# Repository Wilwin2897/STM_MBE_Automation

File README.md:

"# STM_MBE_Automation" 
This is an application program that will provide users with a 
semi-automated platform for controlling the temperature of the substrate heating 
and effusion cells based on several important factors such as the pressure of the 
MBE chamber, together with an automated mechanism for opening and closing 
the cell's shutters. In this way, human errors could be minimized and the user is 
able to obtain all parameters in real-time which are essential for quality control.

Modular control is finished EXCEPT for: Beam Flux Monitor and Filament current source

Live plotting and data logging is only for STM+MBE Combivac pressure gauge, Eurotherms, Lakeshore336, TLC500, Load-Lock pressure Gauge, FUG Voltage

Effusion Cells power sources need to buy serial ethernet cable (which we don't have)
Filament current source and Beam flux monitor has not been integrated in the system

For tutorial on adding a new module, please check the main.py file, all details are included there. 

Hardware connection, just connect the ethernet cable from the network switch to your computer + USB serial cables for the FUG Pressure monitor

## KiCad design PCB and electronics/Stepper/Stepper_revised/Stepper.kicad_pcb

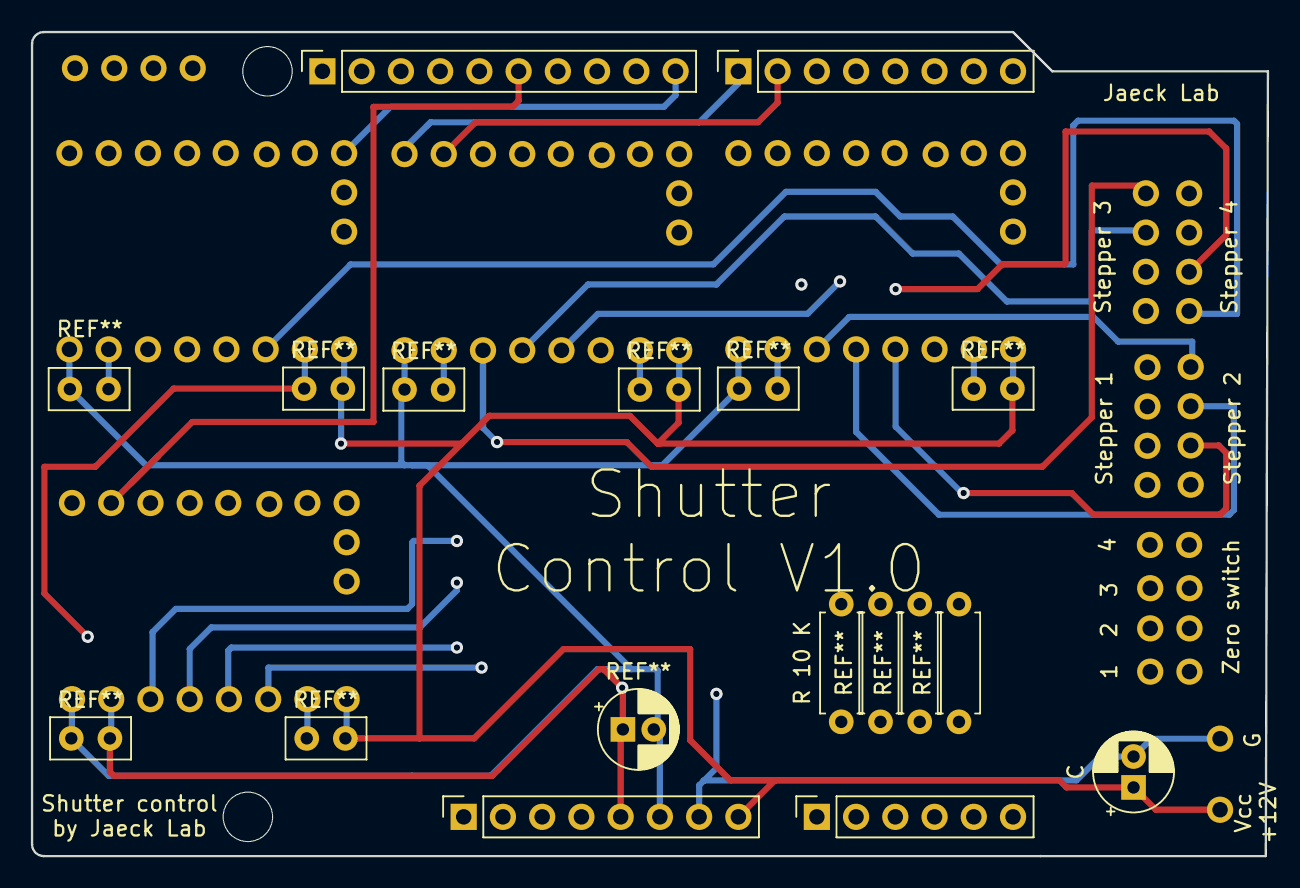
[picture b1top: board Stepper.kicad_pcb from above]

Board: 4 copper layers, 80.0 x 53.3 mm, 8 parts (0 on the bottom side), 3 nets.

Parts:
C: CP; CP_Radial_D5.0mm_P2.00mm
J1: Power; PinSocket_1x08_P2.54mm_Vertical
J2: Digital/PWM; PinSocket_1x10_P2.54mm_Vertical
J3: Analog; PinSocket_1x06_P2.54mm_Vertical
J4: Digital/PWM; PinSocket_1x08_P2.54mm_Vertical
MH1, MH2: MountingHole_3.2mm
R 10 K: R 10K; R_Axial_DIN0207_L6.3mm_D2.5mm_P7.62mm_Horizontal

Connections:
/SCL/A5: J2.1, J3.6
/SDA/A4: J2.2, J3.5
GND: J1.6, J1.7, J2.4

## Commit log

2022-06-23 Initial
2022-06-29 version0.2
2022-08-01 Finished the shutter software and design
2022-08-01 Finished the shutter
2022-08-01 added the PCB parts
2022-10-10 added multithreading, finalized the shutter control, added process controls
2022-10-17 Modular design completed
2022-10-20 Added drag-drop, add-remove button for modular part
2022-10-21 Completing modular control
2022-10-28 Eurotherm control finished
2022-10-28 up one folder
2022-11-18 Finished Eurotherm module part
2022-12-06 Added Fug and Inficon
2022-12-11 small correction
2022-12-23 Version 0.7
2022-12-26 Version 0.7 release
